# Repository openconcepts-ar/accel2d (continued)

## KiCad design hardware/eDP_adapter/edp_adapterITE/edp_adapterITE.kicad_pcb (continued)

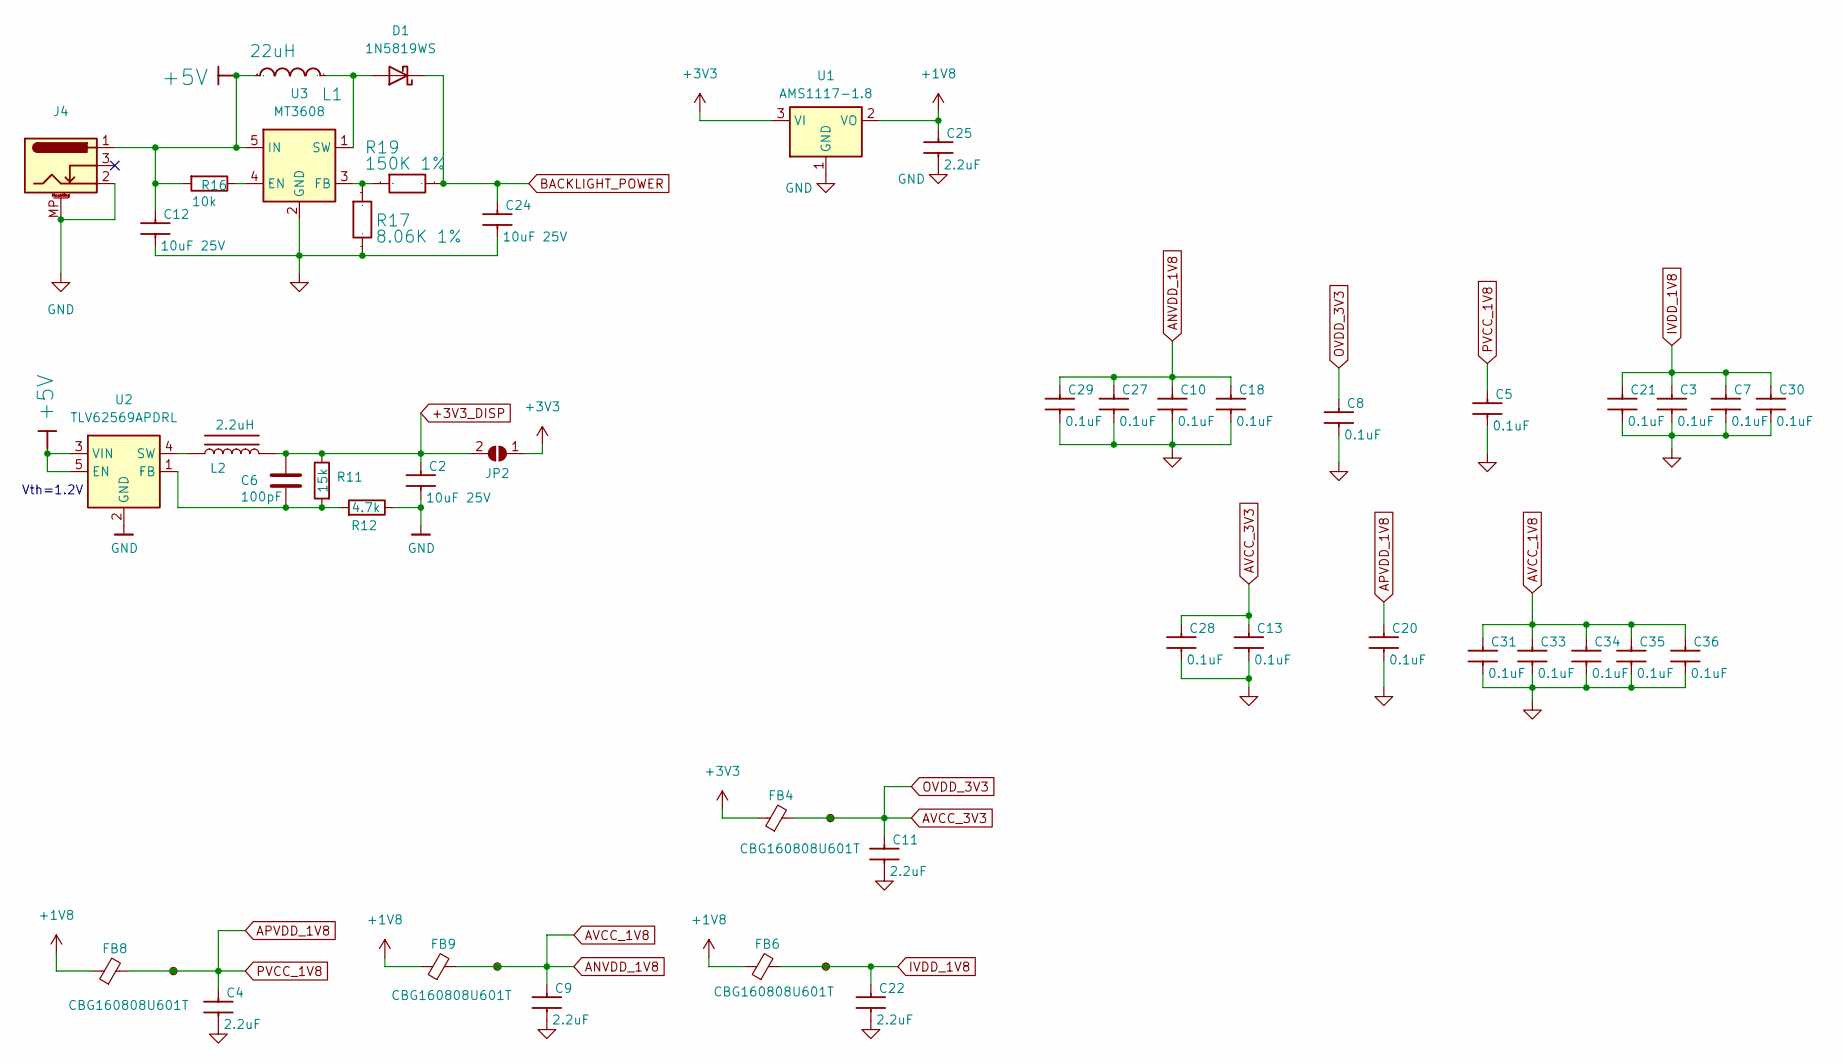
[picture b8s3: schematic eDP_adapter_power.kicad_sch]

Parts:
C2, C12, C24: 10uF 25V; C_0805_2012Metric; MPN TCC0805X5R106K250FT
C3, C5, C7, C8, C10, C13, C18, C20, C21, C27, C28, C29, C30, C31, C33, C34, C35, C36: 0.1uF; C_0402_1005Metric; LCSC Part Number C60474
C4, C9, C11, C22, C25: 2.2uF; C_0402_1005Metric; LCSC Part Number C170151
C6: 100pF; C_0201_0603Metric; MPN GRM033R61C103KA12D
D1: 1N5819WS; D_SOD-323; MPN 1N5819WS
FB4, FB6, FB8, FB9: CBG160808U601T; L_0603_1608Metric; LCSC Part Number C73326
J4: Barrel_Jack_MountingPin; DC-IN-SMD_DC-045A-13A; MPN DC-045A-13A
JP2: SolderJumper_2_Open; SolderJumper-2_P1.3mm_Open_RoundedPad1.0x1.5mm
L1: 22uH; L_Cenker_CKCS4020; LCSC Part Number C5125979
L2: 2.2uH; Murata_DFE201612P-2R2M=P2; LCSC Part Number C79317
R11: 15k; R_0201_0603Metric; MPN RC0201FR-07100KL
R12: 4.7k; R_0201_0603Metric; MPN RC0201FR-07100KL
R16: 10k; R_0402_1005Metric
R17: 8.06K 1%; R_0402_1005Metric; MPN RC0402FR-078K06L
R19: 150K 1%; R_0402_1005Metric
TP1, TP2, TP3, TP8: TestPoint_Small; TestPoint_Pad_D1.0mm
U1: AMS1117-1.8; SOT-223-3_TabPin2
U2: TLV62569APDRL; SOT-563; MPN TLV62569APDRLR
U3: MT3608; SOT-23-6; MPN MT3608

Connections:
+1V8: C25.1, FB6.1, FB8.1, FB9.1, U1.2 (VO)
+3V3: FB4.1, JP2.1 (A), U1.3 (VI); also elsewhere on the board
+3V3_DISP: C2.1, C6.2, JP2.2 (B), L2.1, R11.1; also elsewhere on the board
+5V: C12.1, J4.1, L1.1, R16.2, U2.3 (VIN), U2.5 (EN), U3.5 (IN); also elsewhere on the board
ANVDD_1V8: C9.1, C10.1, C18.1, C27.1, C29.1, C31.1, C33.1, C34.1, C35.1, C36.1, FB9.2, TP2.1; also elsewhere on the board
APVDD_1V8: C4.1, C5.1, C20.1, FB8.2, TP1.1; also elsewhere on the board
AVCC_3V3: C8.1, C11.1, C13.1, C28.1, FB4.2, TP8.1; also elsewhere on the board
BACKLIGHT_POWER: C24.1, D1.1 (K), R19.2; also elsewhere on the board
GND: C2.2, C3.2, C4.2, C5.2, C7.2, C8.2, C9.2, C10.2, C11.2, C12.2, C13.2, C18.2, C20.2, C21.2, C22.2, C24.2, C25.2, C27.2, C28.2, C29.2, C30.2, C31.2, C33.2, C34.2, C35.2, C36.2, J4.2, J4.MP (MountPin), R12.1, R17.2, U1.1 (GND), U2.2 (GND), U3.2 (GND); also elsewhere on the board
IVDD_1V8: C3.1, C7.1, C21.1, C22.1, C30.1, FB6.2, TP3.1; also elsewhere on the board
unnamed: D1.2 (A), L1.2, U3.1 (SW)
unnamed: C6.1, R11.2, R12.2, U2.1 (FB)
unnamed: L2.2, U2.4 (SW)
unnamed: R16.1, U3.4 (EN)
unnamed: R17.1, R19.1, U3.3 (FB)

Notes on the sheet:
Vth=1.2V

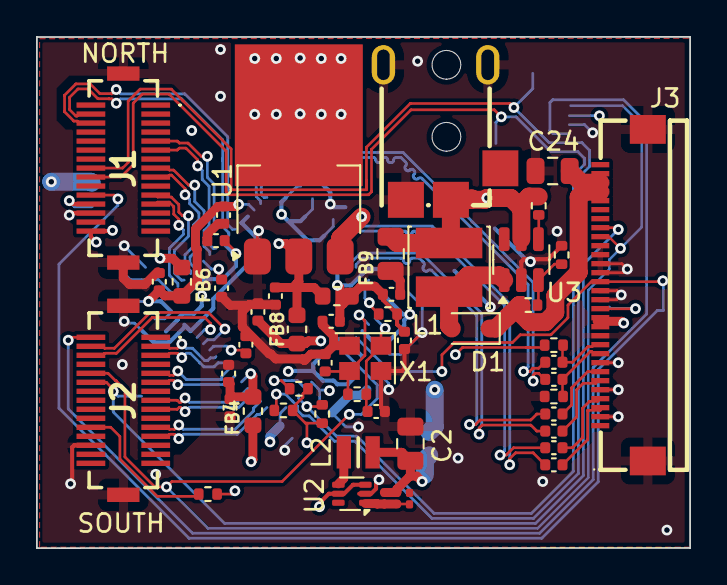
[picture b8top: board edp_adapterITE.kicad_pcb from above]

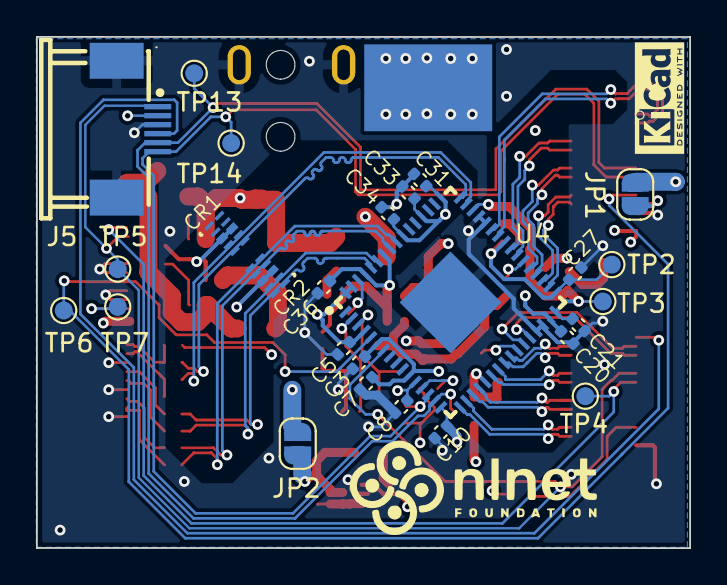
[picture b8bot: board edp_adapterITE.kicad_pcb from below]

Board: 4 copper layers, 36.3 x 28.4 mm, 78 parts (26 on the bottom side), 58 nets.

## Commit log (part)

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2023-08-17 moved tutorial to front page (README.md) and added link to Nlnet funding
2023-08-17 fixed minor HTML typo
2023-08-17 added missing nlnet logo
2023-10-24 line draw primitive & RAM access optimizations
2023-12-08 tested micropython basic demo
2023-12-08 add clock demo (tested in hardware)
2024-01-04 tested baremetal cpu graphics
2024-01-04 sync micropython sources
2024-01-05 fix image names in README.md
2024-04-20 add JPEG decompression support and example
2024-04-20 add PDF schematics
2024-04-20 add CPU board
2024-04-22 add docs for FPGA and CPU boards
2024-04-22 add pictures for FPGA and CPU boards
2024-04-23 fix markdown syntax
2024-04-24 JPEG doc update
2024-04-24 micropython on the CPU doc update
2024-05-08 add support for alternative UART
2024-05-08 add doc images
2024-05-08 add I2C support and example
2024-05-08 add I2C docs
2024-05-09 add doc on how to run micropython scripts from a console using mpremote command
2024-05-09 tested micropython clock demo on the CPU board
2024-05-10 tested movie player (decodes tar of JPEG files)
2024-05-10 add docs for video decoder core
2024-05-10 minor fix
2024-05-10 Update 'DEMOS.md'
    removed eternal video link, added animated GIF file
2024-05-10 add reference to changes to original decoder core
2024-05-13 Add VGA adapter board
2024-05-13 add VGA connector board and docs
2024-05-13 add LVDS adapter board
2024-05-14 add DVI adapter and connector boards
2024-05-14 fix Kicad url and add link to DVI connector board
2024-05-14 fix Kicad url
2024-05-21 add I/O board PCB design files
2024-05-21 tested queue management system demo
2024-05-21 Update 'DEMOS.md'
    replaced html tag <video> for a link to the uploaded file
2024-05-21 fix video link for queue example
2024-05-21 Update 'DEMOS.md'
2024-05-21 Update 'DEMOS.md'
    fix video link
2024-05-21 Update 'DEMOS.md'
    fix video links
2024-05-21 add demo video thumbnail (again)
2024-05-21 Update 'DEMOS.md'
    finally fix video links and thumbnails
2024-05-21 add I/O board docs
2024-05-21 Update 'hardware/README.md'
    typo fix
2024-05-21 Update 'hardware/README.md'
    add reference to the I/O board design files
2024-05-22 Update 'README.md'
    minor tweaks
2024-05-22 lowered resolution of I2C connection example
2024-05-22 add missing files
2024-05-23 add missing files for queue client firmware, and docs
2025-03-11 add basic C++ support
2025-03-12 tested processing API based on AGG 2.4
2025-03-14 add point drawing primitive and update fractal app
2025-03-14 misc fixes and fractal drawing demo tested on hardware
2025-03-18 tested write-back cache and benchmarks
2025-03-20 add FreeType based font demo
2025-03-20 fix font demo image path
2025-03-20 add docs for the canvas demo
2025-03-20 add mising code example pictures for the canvas demo
2025-03-20 fix typo
2025-03-20 add missing picture for canvas demo
2025-09-24 prepare blit demo - just software implementation
2025-09-25 add blitting core and demo
2025-09-25 Squashed 'Nuklear/' content from commit 171090c
    git-subtree-dir: Nuklear
    git-subtree-split: 171090c8e21584330207544dbde5e7c1ec581135
2025-09-26 add very basic Nuklear demo (software rendering)
2025-09-30 Nulkear calculator demo
2025-09-30 add Nuklear's overview & calculator demos
2025-09-30 add documentation about Nuklear demos
2025-10-01 add eDP adapter board design files and documentation
2025-10-01 add embedded CPU debugging documentation
2025-10-01 add scalable font support documentation
2025-10-01 add C++ canvas-like API documentation
2025-10-01 add documentation about supporting C++ in a bare metal project
2025-10-01 add documentation about performance improvements in gateware using a write back cache
2025-10-14 Squashed 'usb_test/main/' content from commit b1837bc
    git-subtree-dir: usb_test/main
    git-subtree-split: b1837bca54f92e7acbe2c3eff7ae1c6b7b6c91d9
2025-10-14 Squashed 'usb_host/' content from commit b1837bc
    git-subtree-dir: usb_host
    git-subtree-split: b1837bca54f92e7acbe2c3eff7ae1c6b7b6c91d9
2025-10-15 port USB soft host implementation to avoid dependency with ESP32 and instead use a standard GPIO interface - initial code - NOT TESTED
2025-10-16 add callbacks, HID detection code (WIP) and misc fixes
2025-10-16 clean code for USB soft host HID management
2025-10-16 basic graphics demo using USB mouse
2025-10-17 make usb demo run in simulation
2025-10-17 add GPIO module to bitstream to allow access to pins by the USB soft host firmware, and demo picture
2025-10-17 add documentation for the USB host feature
2025-10-17 add missing picture of USB demo
2026-01-16 tested line alpha core with pointers
2026-01-16 add missing file to USB demo documentation
2026-04-06 update PCB design files
2026-04-07 misc PCBs update
2026-04-07 Add new boards and changes to current ones
2026-04-07 add missing files for PCBs docs
2026-04-07 minor fix to docs
2026-04-07 minor fix to docs and updated CPU and FPGA board images for docs
2026-04-07 add missing schematics files
2026-04-10 improve documentation regarding 2.5V rail on ECP5 FPGA board
2026-04-28 Add documentation regarding DFM analysis and corresponding changes to the 6-layer board design
2026-04-28 correction of DRC constraints to allow 4-layer boards pass DFM
2026-05-20 add SD test demo
2026-05-20 use previous linker script and startup for the Syterkit-based SD demo
2026-05-21 code cleaning
2026-05-21 add documentation for SD card access demo and new educational demos
2026-05-26 add prototype touch panel test
2026-05-26 add docs for touch panel demo
2026-05-26 add assertions to touch panel demo
2026-05-26 fixed docs for touch panel demo
2026-05-28 tested the i2c touch panel in the CPU board
2026-05-28 update docs for I2C examples
2026-05-29 add image of connected LVDS adapter and reference in docs
2026-06-01 add TFP410 registers setting
2026-06-01 improve report produced by TFP410 I2C control demo, and improve related docs
2026-06-01 improve docs related to TFP410 configuration
2026-06-02 update docs for TFP410 I2C demo reflecting test results
2026-06-09 add docs related to problems with the eDP adapter
2026-06-09 add to documentation an image of the eDP adapter test setup, and minor related corrections
